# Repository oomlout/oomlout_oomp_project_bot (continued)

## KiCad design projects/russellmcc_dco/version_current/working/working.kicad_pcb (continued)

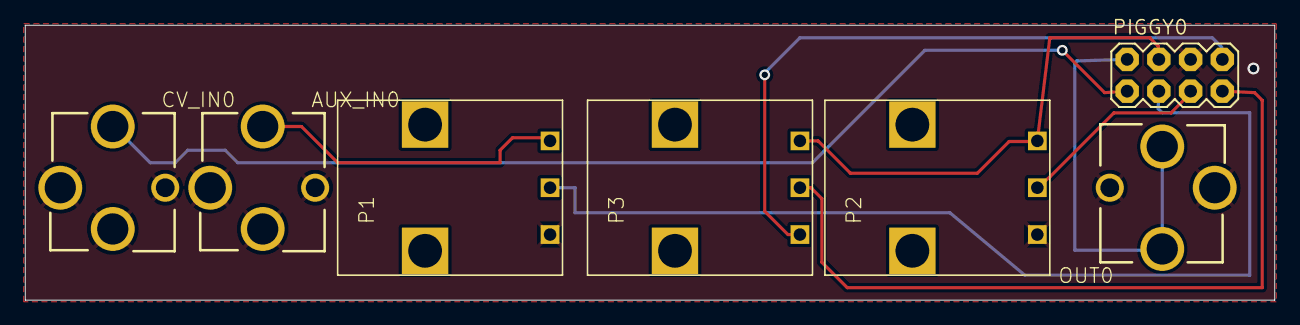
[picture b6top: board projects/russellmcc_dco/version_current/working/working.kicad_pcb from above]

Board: 2 copper layers, 100.0 x 22.0 mm, 7 parts (0 on the bottom side), 9 nets.

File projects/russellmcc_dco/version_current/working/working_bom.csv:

"Id";"Designator";"Footprint";"Quantity";"Designation";"Supplier and ref";
1;"P2,P3,P1";"PDB12";3;"100KB";;;
2;"CV_IN0,AUX_IN0,OUT0";"ERTHENVAR-JACK";3;"AUDIO-JACKERTHENVAR";;;
3;"PIGGY0";"2X4";1;"";;;
